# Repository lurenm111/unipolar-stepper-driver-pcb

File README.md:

<div align="center">
  
</div>

---

<div align="center">

# Unipolar Stepper Motor Driver

### A Hardware-Logic Stepper Motor Driver — No Microcontroller Required

</div>

---

## Abstract

This repository documents a fully discrete, hardware-logic-based unipolar stepper motor driver implemented as a two-layer PCB designed in **KiCad 8.0**. The design deliberately eliminates any dependence on a microcontroller or programmable device, instead realizing the sequencing, direction-control, and power-switching functions entirely through classical digital and analog ICs operating in open-loop.

The signal path is built around a **NE555 timer** configured in astable mode to generate a continuous clock pulse train, a **74LS194 4-bit universal shift register** to implement the four-phase commutation sequence with hardware-selectable direction, and a **7407 hex buffer** (open-collector, non-inverting) to drive the base networks of four **TIP120 NPN Darlington power transistors**. Each transistor drives one motor winding, and a **1N4001 rectifier diode** is placed in a flyback configuration across each winding terminal to suppress the inductive voltage transient at turn-off.

The PCB layout enforces a strict separation of signal and power domains, with independent trace widths calculated from IPC-2221 current-carrying capacity standards. A bottom-layer ground copper pour provides a low-impedance return path, improves thermal dissipation from the power transistors, and reduces susceptibility to radiated emissions from the switching power stage.

---

## Table of Contents

1. [Theoretical Background](#1-theoretical-background)
2. [Circuit Architecture](#2-circuit-architecture)
3. [PCB Layout and Routing Strategy](#3-pcb-layout-and-routing-strategy)
4. [3D Visualization](#4-3d-visualization)
5. [Bottom Layer and Grounding Strategy](#5-bottom-layer-and-grounding-strategy)
6. [Fabrication and Manufacturing Specifications](#6-fabrication-and-manufacturing-specifications)
7. [Repository Structure](#7-repository-structure)
8. [Getting Started](#8-getting-started)
9. [Contributing](#9-contributing)
10. [License](#10-license)

---

## 1. Theoretical Background

The design is derived from a reference circuit published in a practical electronics reference text. The original schematic was adopted as the conceptual baseline and subsequently re-implemented in KiCad 8.0 with component-level refinements, improved footprint selections, and a production-intent PCB layout.

<div align="center">

<table>
  <thead>
    <tr>
      <th align="center">Original Concept — Reference Schematic</th>
      <th align="center">KiCad Implementation — Production Schematic</th>
    </tr>
  </thead>
  <tbody>
    <tr>
      <td align="center">
        
        <br/>
        <sub><b>Figure 1.</b> Reference schematic sourced from a practical electronics textbook. This diagram defines the four-phase unipolar commutation sequence using shift-register logic.</sub>
      </td>
      <td align="center">
        
        <br/>
        <sub><b>Figure 2.</b> KiCad 8.0 schematic implementation (<code>Hardware/Stepper_Motor_Driver.kicad_sch</code>). Hierarchical net labels, ERC-clean, with annotated reference designators.</sub>
      </td>
    </tr>
  </tbody>
</table>

</div>

### Logic Flow

The commutation sequence operates as follows:

| Stage | Active IC | Function |
|---|---|---|
| **1 — Clock Generation** | NE555 (Astable) | Generates a square wave whose frequency is set by R1, R2, and C1. Motor speed is directly proportional to this frequency. |
| **2 — Sequence Generation** | 74LS194 (SRSR / SLSL modes) | The shift register's parallel outputs (QA–QD) cycle through the four-phase binary pattern `1000 → 0100 → 0010 → 0001` (or its reverse). The DIR input pin selects left-shift or right-shift to reverse motor direction. |
| **3 — Signal Buffering** | 7407 (Open-Collector Buffer) | The 74LS194 TTL outputs source insufficient current to reliably drive the TIP120 base resistors at full speed. The 7407 provides open-collector buffering, raising the effective drive current while keeping the logic stage isolated from the power stage. |
| **4 — Power Switching** | TIP120 (Darlington NPN) | Each transistor switches one motor winding to GND. The Darlington configuration (hFE > 1000 typ.) ensures full saturation with the base current available from the 7407 buffer stage. |
| **5 — Flyback Suppression** | 1N4001 (Rectifier Diode) | At turn-off, the collapsing magnetic field in each motor winding generates a counter-EMF spike. The 1N4001 clamps this spike by providing a recirculating path, protecting the TIP120 collector junctions. |

---

## 2. Circuit Architecture

### Component Selection Rationale

| Reference Designator | Component | Key Specification | Design Rationale |
|---|---|---|---|
| U1 | NE555 | Astable, f = 1/(0.693 * C * (R1 + 2R2)) | Industry-standard timer; single supply, wide Vcc range (4.5V–16V), robust output stage. |
| U2 | 74LS194 | 4-bit bi-directional shift register, 20 MHz max | TTL compatible with NE555 output; hardware direction control via S0/S1 mode pins. |
| U3 | 7407 | Hex non-inverting open-collector buffer, 30V/40mA per output | Decouples TTL logic levels from the power-stage base drive; no logic inversion preserves 74LS194 phase sequencing. |
| Q1–Q4 | TIP120 | NPN Darlington, Vce(sat) = 2V, Ic(max) = 5A, hFE > 1000 | Sufficient current gain to switch inductive motor loads; TO-220 package enables heatsinking. |
| D1–D4 | 1N4001 | 50V, 1A rectifier | Standard flyback suppression for inductive loads at the switching frequencies used. |

### Power and Signal Domain Separation

The board operates with two distinct voltage rails:

- **VCC (Logic):** 5V DC, supplied to U1, U2, U3, and pull-up/bias resistors.
- **VMOT (Motor Power):** 5V–12V DC (depending on motor specification), supplied exclusively to the TIP120 collectors and motor winding return paths.

Separating these rails at the connector level prevents switching noise from the power stage from propagating into the sensitive 74LS194 clock and data inputs.

---

## 3. PCB Layout and Routing Strategy

<div align="center">
  
  <br/>
  <sub><b>Figure 3.</b> Front copper layer (F.Cu) routing. Signal traces in the logic domain are clearly distinguishable from the heavier power traces in the motor drive stage.</sub>
</div>

<br/>

### Trace Width Calculation

Trace widths were determined using the **IPC-2221A** external-conductor current-carrying capacity formula:

```
I = k * dT^0.44 * A^0.725
```

Where:
- `I` = maximum current (A)
- `dT` = allowable temperature rise above ambient (deg C)
- `A` = cross-sectional area (mils sq) = width (mils) x copper thickness (mils)
- `k` = 0.048 for external conductors (1 oz / 35 um copper)

The following width classes were established and applied uniformly:

| Domain | Trace Width | Max Current Capacity | Applied To |
|---|---|---|---|
| **Signal / Logic** | 0.3 mm – 0.5 mm | ~0.5 A – 0.9 A | NE555 RC network, 74LS194 data/clock, 7407 inputs/outputs |
| **Power / Motor** | 1.5 mm | ~2.5 A | TIP120 emitter-to-GND, motor winding supply rails, VMOT distribution |

### Routing Guidelines Applied

- **Signal integrity:** All clock and data lines in the logic domain were routed with minimum stub length. The 74LS194 clock input was given priority routing to minimize capacitive loading.
- **Via minimization:** Signal traces were routed on a single layer where possible to avoid introducing via parasitics in the clock path.
- **Power trace topology:** Star topology was used for power distribution to the four TIP120 collector pads, ensuring equal impedance paths to each motor winding drive point.
- **Pad clearance:** A minimum clearance of 0.2 mm (8 mil) was maintained between all copper objects, with an expanded 0.4 mm clearance enforced between power and signal domains.
- **Thermal relief:** Through-hole pads connected to the bottom-layer copper pour include thermal relief spokes to ensure reliable soldering without excessive heat sinking.
- **Design Rule Check (DRC):** The design was verified DRC-clean under KiCad 8.0 rules prior to Gerber export.

---

## 4. 3D Visualization

The following renders were exported from KiCad 8.0's integrated 3D viewer using the VRML/STEP component models.

<div align="center">

<table>
  <tbody>
    <tr>
      <td align="center">
        
        <br/>
        <sub><b>Figure 4.</b> Perspective view demonstrating the physical clearance and orientation of the components, specifically highlighting the aluminum heatsinks mounted on the TIP120 power transistors for thermal management.</sub>
      </td>
      <td align="center">
        
        <br/>
        <sub><b>Figure 5.</b> Front isometric view illustrating the spatial separation between the logic control section (ICs) and the bare TO-220 power transistor array.</sub>
      </td>
      <td align="center">
        
        <br/>
        <sub><b>Figure 6.</b> Top-down orthographic view showing exact component placement, silkscreen annotations, and the underlying top-layer copper routing.</sub>
      </td>
    </tr>
  </tbody>
</table>

</div>

---

## 5. Bottom Layer and Grounding Strategy

<div align="center">
  
  <br/>
  <sub><b>Figure 7.</b> Bottom copper layer (B.Cu) showing the solid GND copper pour. The pour fills virtually the entire bottom layer, providing a continuous low-impedance ground plane.</sub>
</div>

<br/>

### Copper Pour Implementation

The bottom layer (B.Cu) is defined as a single net fill assigned to the **GND** net. The fill was configured with the following parameters in KiCad:

| Parameter | Value |
|---|---|
| Net | GND |
| Fill Type | Solid |
| Minimum Width | 0.25 mm |
| Pad Connection | Thermal Relief (4 spokes, 0.5 mm spoke width) |
| Island Removal | Remove isolated islands |
| Priority Level | 0 (highest fill priority) |

### Functional Rationale

A solid GND pour on the bottom layer serves three distinct engineering purposes in this design:

1. **Low-Impedance Return Path:** The four TIP120 transistors switch currents up to several amperes through motor windings. A solid ground plane provides a near-zero-inductance return path for these pulsed currents, preventing GND bounce that would corrupt the TTL logic levels at U2 and U3.

2. **Thermal Dissipation:** The TIP120 in TO-220 package dissipates power as P_D = Vce(sat) * Ic. At Vce(sat) approximately 2V and Ic = 1A per winding, each transistor dissipates approximately 2W. The copper pour thermally couples to the PCB substrate and distributes this heat across a larger area, supplementing (but not replacing) any external heatsink attached to the TO-220 tab.

3. **EMI Reduction:** Switching transients from the inductive motor windings generate common-mode noise. The solid copper pour, when connected to protective earth (PE) in the system enclosure, provides a low-impedance path for displacement currents to return to their source, reducing radiated emissions from the PCB.

---

## 6. Fabrication and Manufacturing Specifications

Gerber files and drill files are pre-generated and available in the `Fabrication/` directory, ready for immediate submission to any standard PCB fabrication service.

### Gerber File Manifest

| File | Layer Description |
|---|---|
| `Stepper_Motor_Driver-F_Cu.gbr` | Front copper layer |
| `Stepper_Motor_Driver-B_Cu.gbr` | Back copper layer (GND pour) |
| `Stepper_Motor_Driver-F_Mask.gbr` | Front solder mask |
| `Stepper_Motor_Driver-B_Mask.gbr` | Back solder mask |
| `Stepper_Motor_Driver-F_Silkscreen.gbr` | Front silkscreen (component references) |
| `Stepper_Motor_Driver-B_Silkscreen.gbr` | Back silkscreen |
| `Stepper_Motor_Driver-F_Paste.gbr` | Front solder paste |
| `Stepper_Motor_Driver-B_Paste.gbr` | Back solder paste |
| `Stepper_Motor_Driver-Edge_Cuts.gbr` | Board outline |
| `Stepper_Motor_Driver-PTH.drl` | Plated through-hole drill file |
| `Stepper_Motor_Driver-NPTH.drl` | Non-plated through-hole drill file |
| `Stepper_Motor_Driver-job.gbrjob` | Gerber job file |

### Recommended PCB Fabrication Parameters

| Parameter | Specification |
|---|---|
| **Board Material** | FR4 (Tg 130 deg C minimum) |
| **Board Thickness** | 1.6 mm |
| **Copper Weight** | 1 oz (35 um) — all layers |
| **Layers** | 2 |
| **Minimum Trace Width** | 0.3 mm |
| **Minimum Clearance** | 0.2 mm |
| **Minimum Drill Size** | 0.8 mm |
| **Surface Finish** | HASL (Lead-free) or ENIG |
| **Solder Mask Color** | Green (standard); any color accepted |
| **Silkscreen** | White |
| **PCB Quantity (minimum)** | 5 (typical fab minimum) |

### Generating Gerbers from Source

1. Open `Hardware/Stepper_Motor_Driver.kicad_pro` in KiCad 8.0.
2. Open the PCB Editor (PCBnew).
3. Navigate to **File > Fabrication Outputs > Gerbers (.gbr)**.
4. Set the output directory to `Fabrication/`.
5. Select all layers and enable **Use drill/place file origin**.
6. Click **Plot**, then **Generate Drill Files** from the same dialog.
7. Verify the output against the file manifest above.

---

## 7. Repository Structure

```
Unipolar Stepper Motor Driver/
|
|-- Hardware/                           # KiCad 8.0 source files
|   |-- Stepper_Motor_Driver.kicad_pro  # Project file
|   |-- Stepper_Motor_Driver.kicad_sch  # Schematic
|   |-- Stepper_Motor_Driver.kicad_pcb  # PCB layout
|
|-- Fabrication/                        # Production-ready Gerber and drill files
|   |-- *.gbr                           # Gerber layers
|   |-- *.drl                           # Drill files
|   |-- *-job.gbrjob                    # Gerber job descriptor
|
|-- Images/                             # Documentation images and renders
|   |-- 3dboard view-ai generated.jpeg  # AI-enhanced 3D banner render
|   |-- Schematic From Practical        # Original reference schematic
|       Electronics Book.png
|   |-- schematic diagram.png           # KiCad schematic export
|   |-- pcb routing.png                 # PCB front copper routing
|   |-- 3d view.png                     # KiCad 3D render -- isometric
|   |-- 3d view 1.png                   # KiCad 3D render -- top-down
|   |-- 3d view 2.png                   # KiCad 3D render -- perspective
|   |-- 3d back.png                     # KiCad 3D render -- bottom layer
|
|-- Docs/                               # Additional documentation
|-- README.md                           # This file
|-- CONTRIBUTING.md                     # Contributor guidelines
|-- LICENSE                             # CERN-OHL-S v2 license text
```

---

## 8. Getting Started

### Prerequisites

- [KiCad 8.0](https://www.kicad.org/download/) installed on your system.
- A standard Gerber viewer (e.g., gerbv, KiCad Gerber Viewer) for verifying fabrication files.

### Viewing the Design

```bash
# Clone the repository
git clone https://github.com/<your-username>/unipolar-stepper-motor-driver.git

# Open the KiCad project file
# Navigate to: Hardware/Stepper_Motor_Driver.kicad_pro
# Open with KiCad 8.0
```

### Bill of Materials (BOM) Summary

| Qty | Reference | Part | Package |
|---|---|---|---|
| 1 | U1 | NE555P | DIP-8 |
| 1 | U2 | 74LS194N | DIP-16 |
| 1 | U3 | 7407N | DIP-14 |
| 4 | Q1-Q4 | TIP120 | TO-220 |
| 4 | D1-D4 | 1N4001 | DO-41 |
| 2 | R1, R2 | Resistor (per NE555 design) | Axial |
| 1 | C1 | Capacitor (per NE555 design) | Radial |
| — | — | Decoupling capacitors (100nF per IC) | Radial / Disc |

> Refer to the schematic (`Hardware/Stepper_Motor_Driver.kicad_sch`) for the complete BOM with exact values, net names, and reference designators.

---

## 9. Contributing

Contributions to this project are welcome and encouraged. Please read the [CONTRIBUTING.md](CONTRIBUTING.md) file for detailed guidelines on how to report hardware bugs, propose schematic changes, follow PCB layout conventions, and submit pull requests for KiCad source files.

---

## 10. License

This hardware design is released under the **CERN Open Hardware Licence Version 2 — Strongly Reciprocal (CERN-OHL-S v2)**.

You are free to study, modify, distribute, and manufacture this design, provided that any modifications or derivative works are released under the same license. Commercial use is permitted under these terms.

Full license text is available in the [`LICENSE`](LICENSE) file in this repository.

> CERN-OHL-S v2: [https://ohwr.org/cern_ohl_s_v2.txt](https://ohwr.org/cern_ohl_s_v2.txt)

---

<div align="center">

Designed with KiCad 8.0 | Licensed under CERN-OHL-S v2 | Open Source Hardware

</div>

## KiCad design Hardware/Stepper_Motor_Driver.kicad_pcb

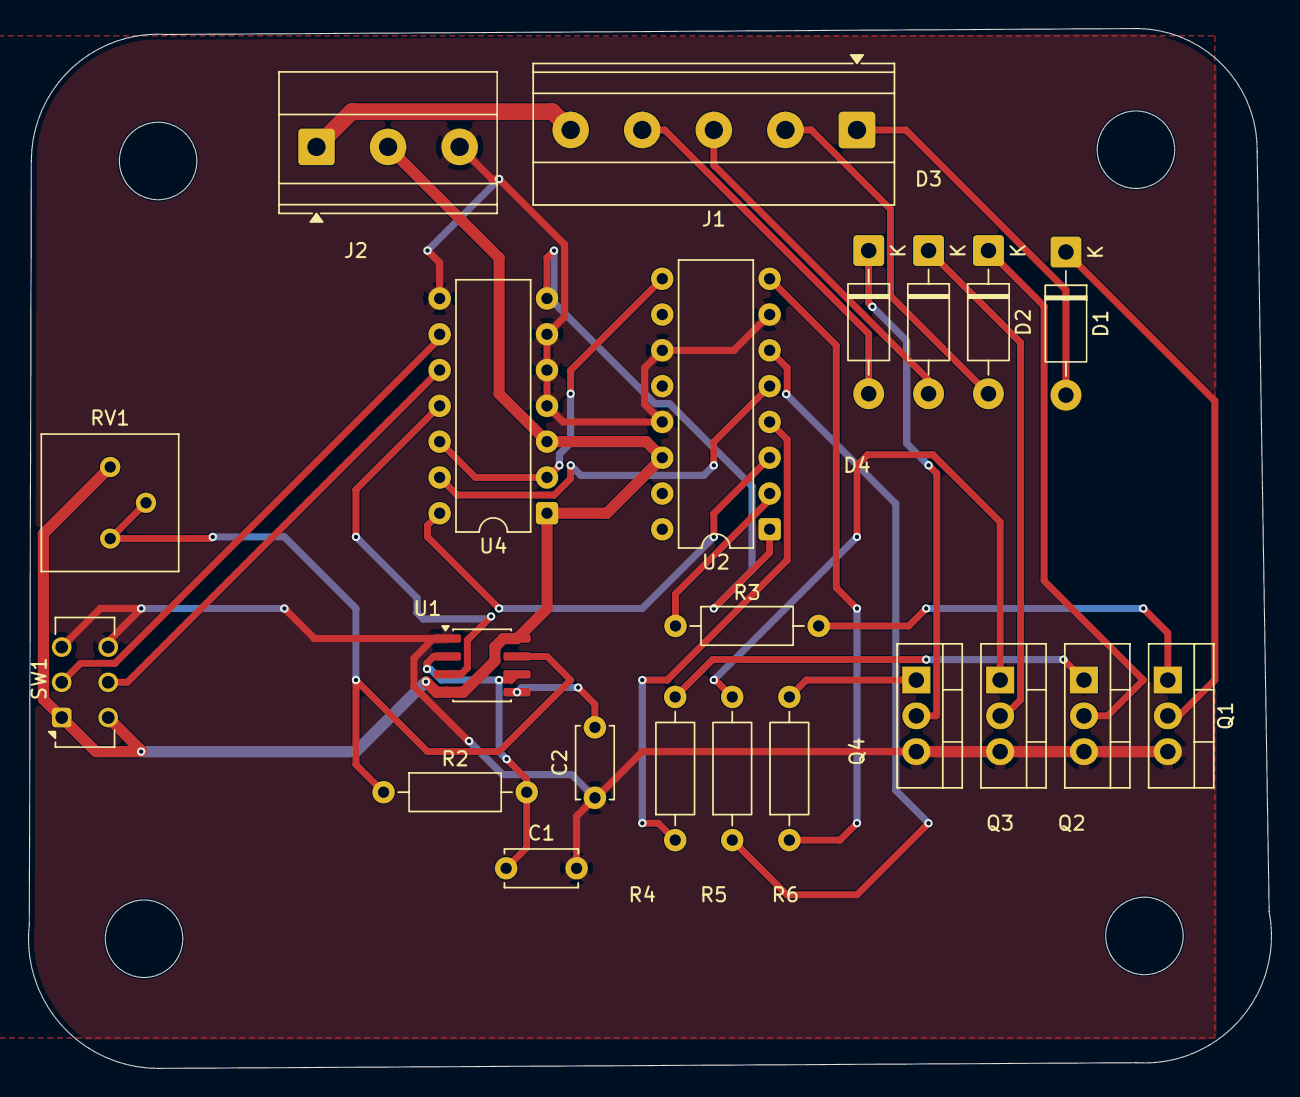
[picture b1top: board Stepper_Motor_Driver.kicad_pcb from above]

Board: 2 copper layers, 88.2 x 73.8 mm, 26 parts (0 on the bottom side), 29 nets.

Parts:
C1, C2: 0.01uF; C_Disc_D5.0mm_W2.5mm_P5.00mm
D1, D2, D3, D4: 1N4001; D_DO-41_SOD81_P10.16mm_Horizontal
H1, H2, H3, H4: MountingHole; MountingHole_5.5mm
J1: Conn_01x05; TerminalBlock_Phoenix_MKDS-1,5-5-5.08_1x05_P5.08mm_Horizont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
J2: Conn_01x03; TerminalBlock_Phoenix_MKDS-1,5-3-5.08_1x03_P5.08mm_Horizont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
Q1, Q2, Q3, Q4: TIP120; TO-220-3_Vertical
R2, R3, R4, R5, R6: 1K; R_Axial_DIN0207_L6.3mm_D2.5mm_P10.16mm_Horizontal
RV1: 1M; Potentiometer_Bourns_3386P_Vertical
SW1: SW_Push_DPDT; SW_CK_JS202011CQN_DPDT_Straight
U1: NE555D; SOIC-8_3.9x4.9mm_P1.27mm
U2: 7407; DIP-16_W7.62mm
U4: 74LS194; DIP-14_W7.62mm

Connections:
+5V: J2.2, RV1.3, SW1.1 (A), SW1.6 (C), U1.4 (~RST), U1.8 (VCC), U2.14 (VCC), U4.1 (Mr), U4.3 (P0)
+12V: J1.5, J2.1
GNDREF: C1.2, C2.1, J2.3, Q1.3 (E), Q2.3 (E), Q3.3 (E), Q4.3 (E), SW1.3 (C), SW1.4 (A), U1.1 (GND), U2.7 (GND), U2.11, U2.13, U4.4 (P1), U4.5 (P2), U4.6 (P3), U4.8 (GND)
unnamed: D1.2 (A), J1.1
unnamed: D1.1 (K), Q1.2 (C)
unnamed: D2.2 (A), J1.2
unnamed: D2.1 (K), Q2.2 (C)
unnamed: D3.2 (A), J1.3
unnamed: D3.1 (K), Q3.2 (C)
unnamed: D4.2 (A), J1.4
unnamed: D4.1 (K), Q4.2 (C)
unnamed: Q1.1 (B), R3.2
unnamed: Q2.1 (B), R4.2
unnamed: Q3.1 (B), R5.2
unnamed: Q4.1 (B), R6.2
unnamed: R3.1, U2.2
unnamed: R4.1, U2.4
unnamed: R5.1, U2.6
unnamed: R6.1, U2.8
unnamed: C2.2, U1.5 (CONT)
unnamed: R2.1, RV1.1, RV1.2, U1.7 (DISCH)
unnamed: U1.3 (OUT), U4.11 (Cp)
unnamed: C1.1, R2.2, U1.2 (TRIG), U1.6 (THRES)
unnamed: U2.1, U4.7 (Dsl)
unnamed: U2.9, U4.2 (Dsr), U4.12 (Q3)
unnamed: U2.3, U4.14 (Q1)
unnamed: U2.5, U4.13 (Q2)
unnamed: SW1.2 (B), U4.9 (S0)
unnamed: SW1.5 (B), U4.10 (S1)
